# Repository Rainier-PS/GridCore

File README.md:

# GridCore

> GridCore is a minimalist reaction-based game system built on a 2×2 LED grid with 4 buttons. Modular. Expandable. Fun.

## What is GridCore?

GridCore is a lightweight, open-source mini game console using only 4 buttons and a 2×2 LED grid. GridCore is designed to be fun, hackable, and extendable. It runs simple games like reaction challenges with plans for more in future updates. (more games)

## Images

### Schematic

### PCB Layout

### PCB Front (Render)

### PCB Back (Render)

### GridCore Board - Front

### GridCore Board - Back

## Features

- Reaction-based game logic that gets harder with each level
- Built-in splash screen animation
- MX keys 4-button control
- Organized, human-readable code
- Easily expandable architecture for additional games/tools

## How to Play

- Watch for a random LED to light up.
- Press the corresponding button as fast as possible.
- Get it right? You level up and it gets faster.
- Miss or timeout? The game restarts.

**Button–LED Layout**  
(Button position ≠ LED index)

| Button No. | Position     | LED No. | LED Position    |
|------------|--------------|---------|-----------------|
| Button 1   | Top Left     | LED 3   | Upper Right     |
| Button 2   | Top Right    | LED 2   | Upper Left      |
| Button 3   | Bottom Left  | LED 1   | Lower Left      |
| Button 4   | Bottom Right | LED 4   | Lower Right     |

## Future Plans

- Add multiple minigames (reaction, memory, binary input)
- Tool modes (timer, counter, morse trainer, etc)

## Getting Started

### 1. Flash the Code

Upload the `GridCore.ino` sketch to your board using Arduino IDE or PlatformIO.

### 2. Wiring

| Function | GPIO Pin | Notes         |
|----------|----------|---------------|
| Button 1 | GPIO26   | Pull-down     |
| Button 2 | GPIO27   | Pull-down     |
| Button 3 | GPIO28   | Pull-down     |
| Button 4 | GPIO29   | Pull-down     |
| LED 1    | GPIO0    | Lower Left    |
| LED 2    | GPIO7    | Upper Left    |
| LED 3    | GPIO6    | Upper Right   |
| LED 4    | GPIO1    | Lower Right   |

## Advanced Notes

- **GND Test Pad**  
  A dedicated exposed GND pad is included on the PCB for easy multimeter probing and diagnostics. Useful during debugging or for adding temporary modules or sensors.

- **Dual Pin Headers for Xiao**  
  The Xiao RP2040 footprint includes **double/duplicate pin holes**, one for standard mounting, and another inline set for breakout or jumper wiring. This allows GridCore to be used not only as a game system, but also as a **hackable Xiao devboard** for rapid prototyping.

> **Note**  
> This project has passed both ERC (Electrical Rule Check) and DRC (Design Rule Check) with no errors. All submission requirements for Pathfinder have been completed.

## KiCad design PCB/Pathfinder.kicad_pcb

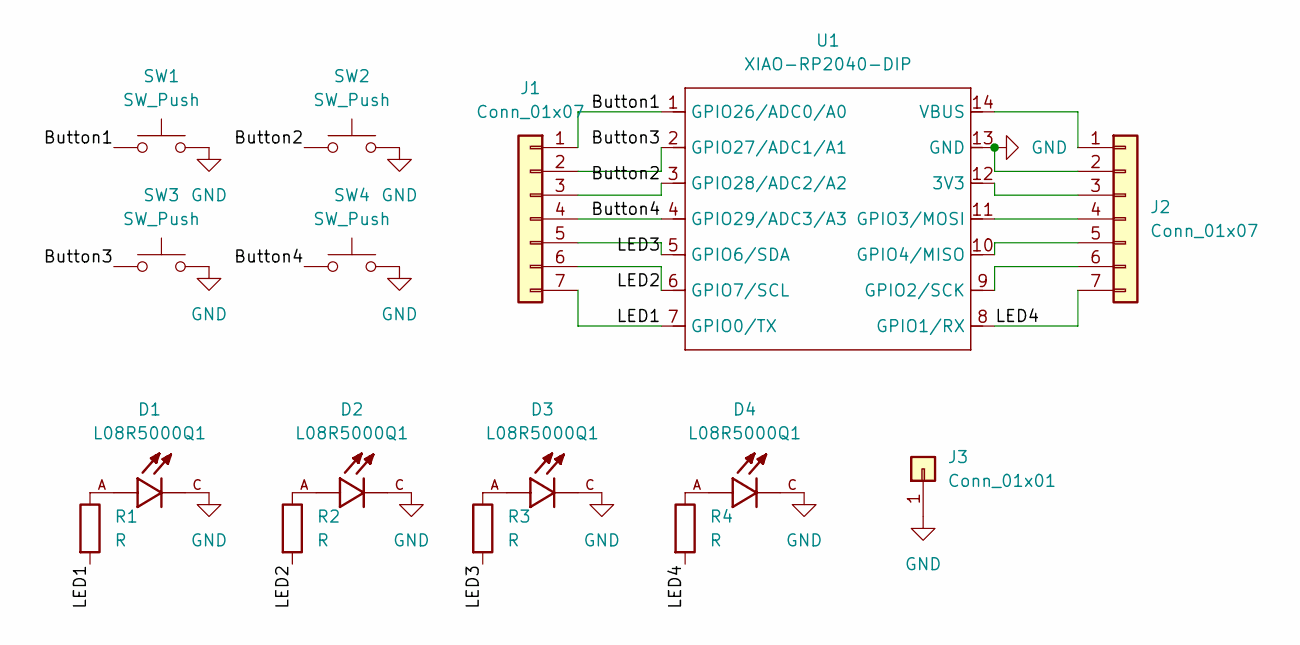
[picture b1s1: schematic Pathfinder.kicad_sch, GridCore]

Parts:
D1, D2, D3, D4: L08R5000Q1; LEDRD254W57D500H1070; PARTREV NA
J1, J2: Conn_01x07; PinHeader_1x07_P2.54mm_Vertical
J3: Conn_01x01; TestPoint_THTPad_D1.5mm_Drill0.7mm
R1, R2, R3, R4: R; R_Axial_DIN0204_L3.6mm_D1.6mm_P5.08mm_Horizontal
SW1, SW2, SW3, SW4: SW_Push; SW_Cherry_MX_1.00u_PCB
U1: XIAO-RP2040-DIP

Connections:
/Button1: J1.1, SW1.1, U1.1 (GPIO26/ADC0/A0); also elsewhere on the board
/Button2: J1.3, SW2.1, U1.3 (GPIO28/ADC2/A2); also elsewhere on the board
/Button3: J1.2, SW3.1, U1.2 (GPIO27/ADC1/A1); also elsewhere on the board
/Button4: J1.4, SW4.1, U1.4 (GPIO29/ADC3/A3); also elsewhere on the board
/LED1: J1.7, R1.2, U1.7 (GPIO0/TX); also elsewhere on the board
/LED2: J1.6, R2.2, U1.6 (GPIO7/SCL); also elsewhere on the board
/LED3: J1.5, R3.2, U1.5 (GPIO6/SDA); also elsewhere on the board
/LED4: J2.7, R4.2, U1.8 (GPIO1/RX); also elsewhere on the board
GND: D1.C, D2.C, D3.C, D4.C, J2.2, J3.1, SW1.2, SW2.2, SW3.2, SW4.2, U1.13 (GND); also elsewhere on the board
unnamed: D1.A, R1.1
unnamed: D2.A, R2.1
unnamed: D3.A, R3.1
unnamed: D4.A, R4.1
unnamed 13: J2.1, U1.14 (VBUS); also elsewhere on the board
unnamed 14: J2.3, U1.12 (3V3); also elsewhere on the board
unnamed 15: J2.4, U1.11 (GPIO3/MOSI); also elsewhere on the board
unnamed 16: J2.5, U1.10 (GPIO4/MISO); also elsewhere on the board
unnamed 17: J2.6, U1.9 (GPIO2/SCK); also elsewhere on the board

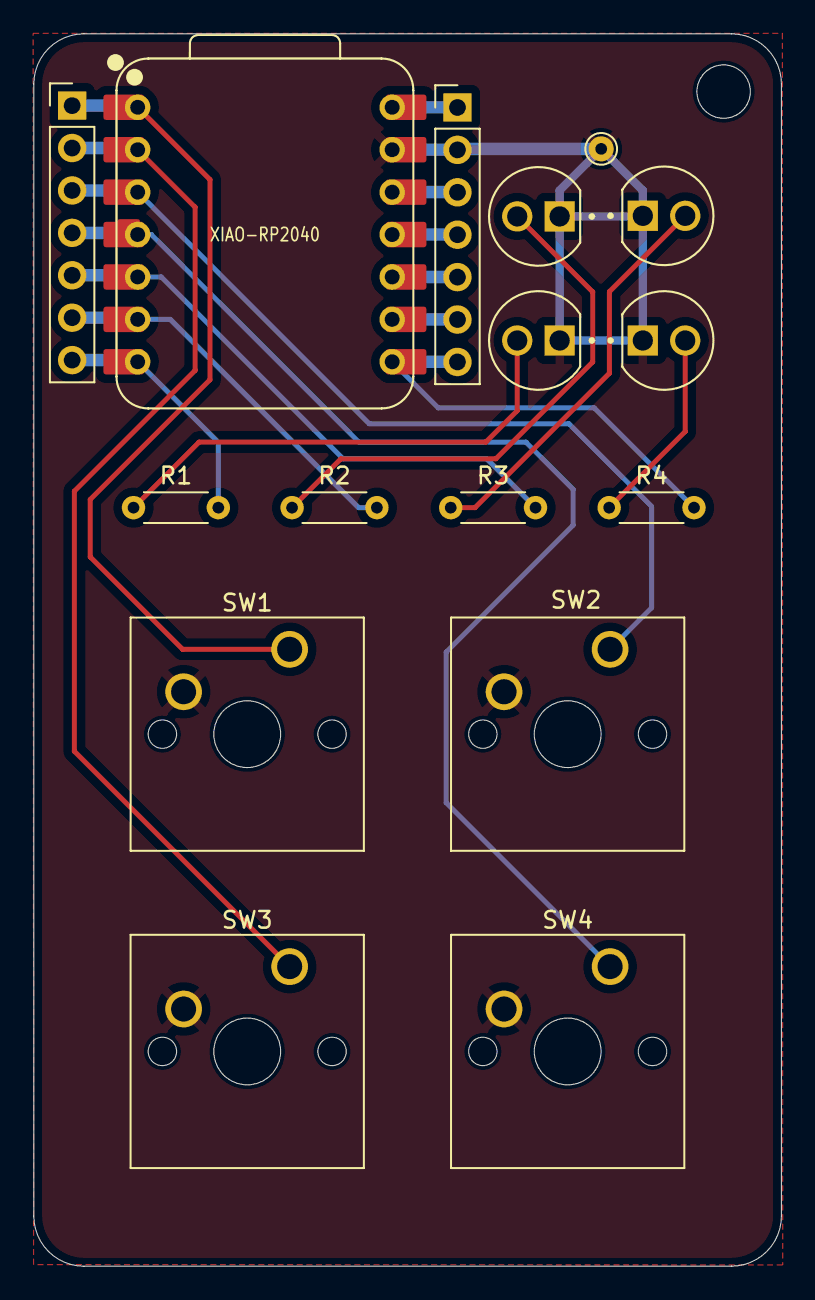
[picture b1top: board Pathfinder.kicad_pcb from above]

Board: 2 copper layers, 44.8 x 73.8 mm, 16 parts (0 on the bottom side), 18 nets.

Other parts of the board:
XIAO-RP2040: XIAO-RP2040-DIP

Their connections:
/Button1: XIAO-RP2040.1 (GPIO26/ADC0/A0); also elsewhere on the board
/Button2: XIAO-RP2040.3 (GPIO28/ADC2/A2); also elsewhere on the board
/Button3: XIAO-RP2040.2 (GPIO27/ADC1/A1); also elsewhere on the board
/Button4: XIAO-RP2040.4 (GPIO29/ADC3/A3); also elsewhere on the board
/LED1: XIAO-RP2040.7 (GPIO0/TX); also elsewhere on the board
/LED2: XIAO-RP2040.6 (GPIO7/SCL); also elsewhere on the board
/LED3: XIAO-RP2040.5 (GPIO6/SDA); also elsewhere on the board
/LED4: XIAO-RP2040.8 (GPIO1/RX); also elsewhere on the board
GND: XIAO-RP2040.13 (GND); also elsewhere on the board
unnamed 13: XIAO-RP2040.14 (VBUS); also elsewhere on the board
unnamed 14: XIAO-RP2040.12 (3V3); also elsewhere on the board
unnamed 15: XIAO-RP2040.11 (GPIO3/MOSI); also elsewhere on the board
unnamed 16: XIAO-RP2040.10 (GPIO4/MISO); also elsewhere on the board
unnamed 17: XIAO-RP2040.9 (GPIO2/SCK); also elsewhere on the board

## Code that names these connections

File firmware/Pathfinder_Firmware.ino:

const int buttonPins[4] = {26, 27, 28, 29};  // BTN1 (TL), BTN2 (TR), BTN3 (BL), BTN4 (BR)
const int ledPins[4] = {0, 7, 6, 1};         // LED1 (BL), LED2 (TL), LED3 (TR), LED4 (BR)

int currentLed = -1;
int score = 0;
bool gameStarted = false;
bool waitingForInput = false;
unsigned long reactionStart = 0;
unsigned long timeLimit = 3000;  // starts at 3000 ms

void setup() {
  for (int i = 0; i < 4; i++) {
    pinMode(buttonPins[i], INPUT_PULLUP);
    pinMode(ledPins[i], OUTPUT);
    digitalWrite(ledPins[i], LOW);
  }
  splashScreen();
}

void loop() {
  if (!gameStarted) {
    delay(1000);
    startRound();
    gameStarted = true;
  }

  if (waitingForInput) {
    for (int i = 0; i < 4; i++) {
      if (digitalRead(buttonPins[i]) == LOW) {
        handleInput(i);
        break;
      }
    }

    if (millis() - reactionStart > timeLimit) {
      showFail();
      resetGame();
    }
  }
}

void splashScreen() {
  for (int i = 0; i < 4; i++) {
    digitalWrite(ledPins[i], HIGH);
    delay(150);
  }
  for (int i = 0; i < 4; i++) {
    digitalWrite(ledPins[i], LOW);
    delay(150);
  }
}

void startRound() {
  currentLed = random(0, 4);
  digitalWrite(ledPins[currentLed], HIGH);
  reactionStart = millis();
  waitingForInput = true;
}

void handleInput(int buttonIndex) {
  waitingForInput = false;
  digitalWrite(ledPins[currentLed], LOW);

  if (buttonIndex == currentLed) {
    showSuccess();
    score++;
    timeLimit = max(1000, 3000 - (score * 200)); // reduce time per round
  } else {
    showFail();
    resetGame();
  }

  delay(1000);
  gameStarted = false;
}

void showSuccess() {
  for (int i = 0; i < 2; i++) {
    allLeds(HIGH);
    delay(150);
    allLeds(LOW);
    delay(150);
  }
}

void showFail() {
  for (int i = 0; i < 2; i++) {
    digitalWrite(ledPins[currentLed], HIGH);
    delay(150);
    digitalWrite(ledPins[currentLed], LOW);
    delay(150);
  }
}

void allLeds(bool state) {
  for (int i = 0; i < 4; i++) {
    digitalWrite(ledPins[i], state);
  }
}

void resetGame() {
  score = 0;
  timeLimit = 3000;
  waitingForInput = false;
  gameStarted = false;
}

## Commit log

2025-07-25 Create temp
